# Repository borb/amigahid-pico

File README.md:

# amigahid-pico

please note: the interesting stuff goes into the [development](https://github.com/borb/amigahid-pico/tree/development) branch, so if main seems slow, check it out.

## introduction

amigahid-pico uses the rp2040 microcontroller (e.g. the raspberry pi pico) in a carrier board to attach usb input devices to a standard amiga without the need for a usb stack on the amiga itself.

it currently supports keyboards and mice and provides connection via the internal keyboard connector, the rj11/din socket on big-box amigas, and via the controller ports.

**this project is very much a work in progress.**

## **important note**

* current kicad files are for r5 pcb, pin mappings are not yet in the source tree! i have not yet generated this board as a pcb, but it is mostly identical to r4. the keyboard and controller port 1 are correct at time of writing, and will be fixed for the second controller port when the next prototype arrives.

* **always read the [errata](./doc/errata.md) section for the current pcb layout before deciding whether or not to build.**

## documentation

* [installation](./doc/installation.md)
* [hardware](./doc/hardware.md)
* [errors in revisions (errata)](./doc/errata.md)

## history

this project is a rewrite of the [amigahid](https://github.com/borb/amigahid) project to the rp2040 microcontroller.

originally, after the retirement of the arduino adk board and shortening availability of the max3421e "usb host shield" for arduino boards, the need for a cheap, easy and continually available replacement was sought.

at first, the uhs mini via a level shifter seemed ideal, but significant issues were found convincing it to work with a variety of arduino boards.

the rp2040 made sense as a target because it is widely available, has sufficient physical connections and is powerful enough to meet multiple needs.

## what is the latency of this?

i have not measured the latency, but the keyboard signals are sent out the moment they are received on the usb bus. the potential latency is likely fractionally longer than the amiga mcu but bear in mind the rp2040 is significantly faster than the standard amiga keyboard controller.

## roadmap

please see the issues tab on the [github repository](https://github.com/borb/amigahid-pico) for the current list of planned features. the tl;dr is:

normal:
* i<sup>2</sup>c display for config/status
* controller emulation
    * keyboard-based controller emulation (use udlr for directions?)
* flash memory-based configuration
* possible amiga-side control panel (using bidirectional controller port signals)
* rotary control simulation (for controlling gotek drives)

crazy talk:
* non-amiga support
* non-hidbp support
* analogue/paddle emulation
* fix some tinyusb issues (hotplug, timing-related instability)

## license

on the fence at the moment, but the current license choice is Eclipse Public License 2.0 (EPL-2.0).

## third party licenses

* µgui: this code contains 'µgui' by achim döbler; the license for this can be read at in the [display readme](./src/display/README.md)

## whuh... who?

nine <[nine@aphlor.org](mailto:nine@aphlor.org)>

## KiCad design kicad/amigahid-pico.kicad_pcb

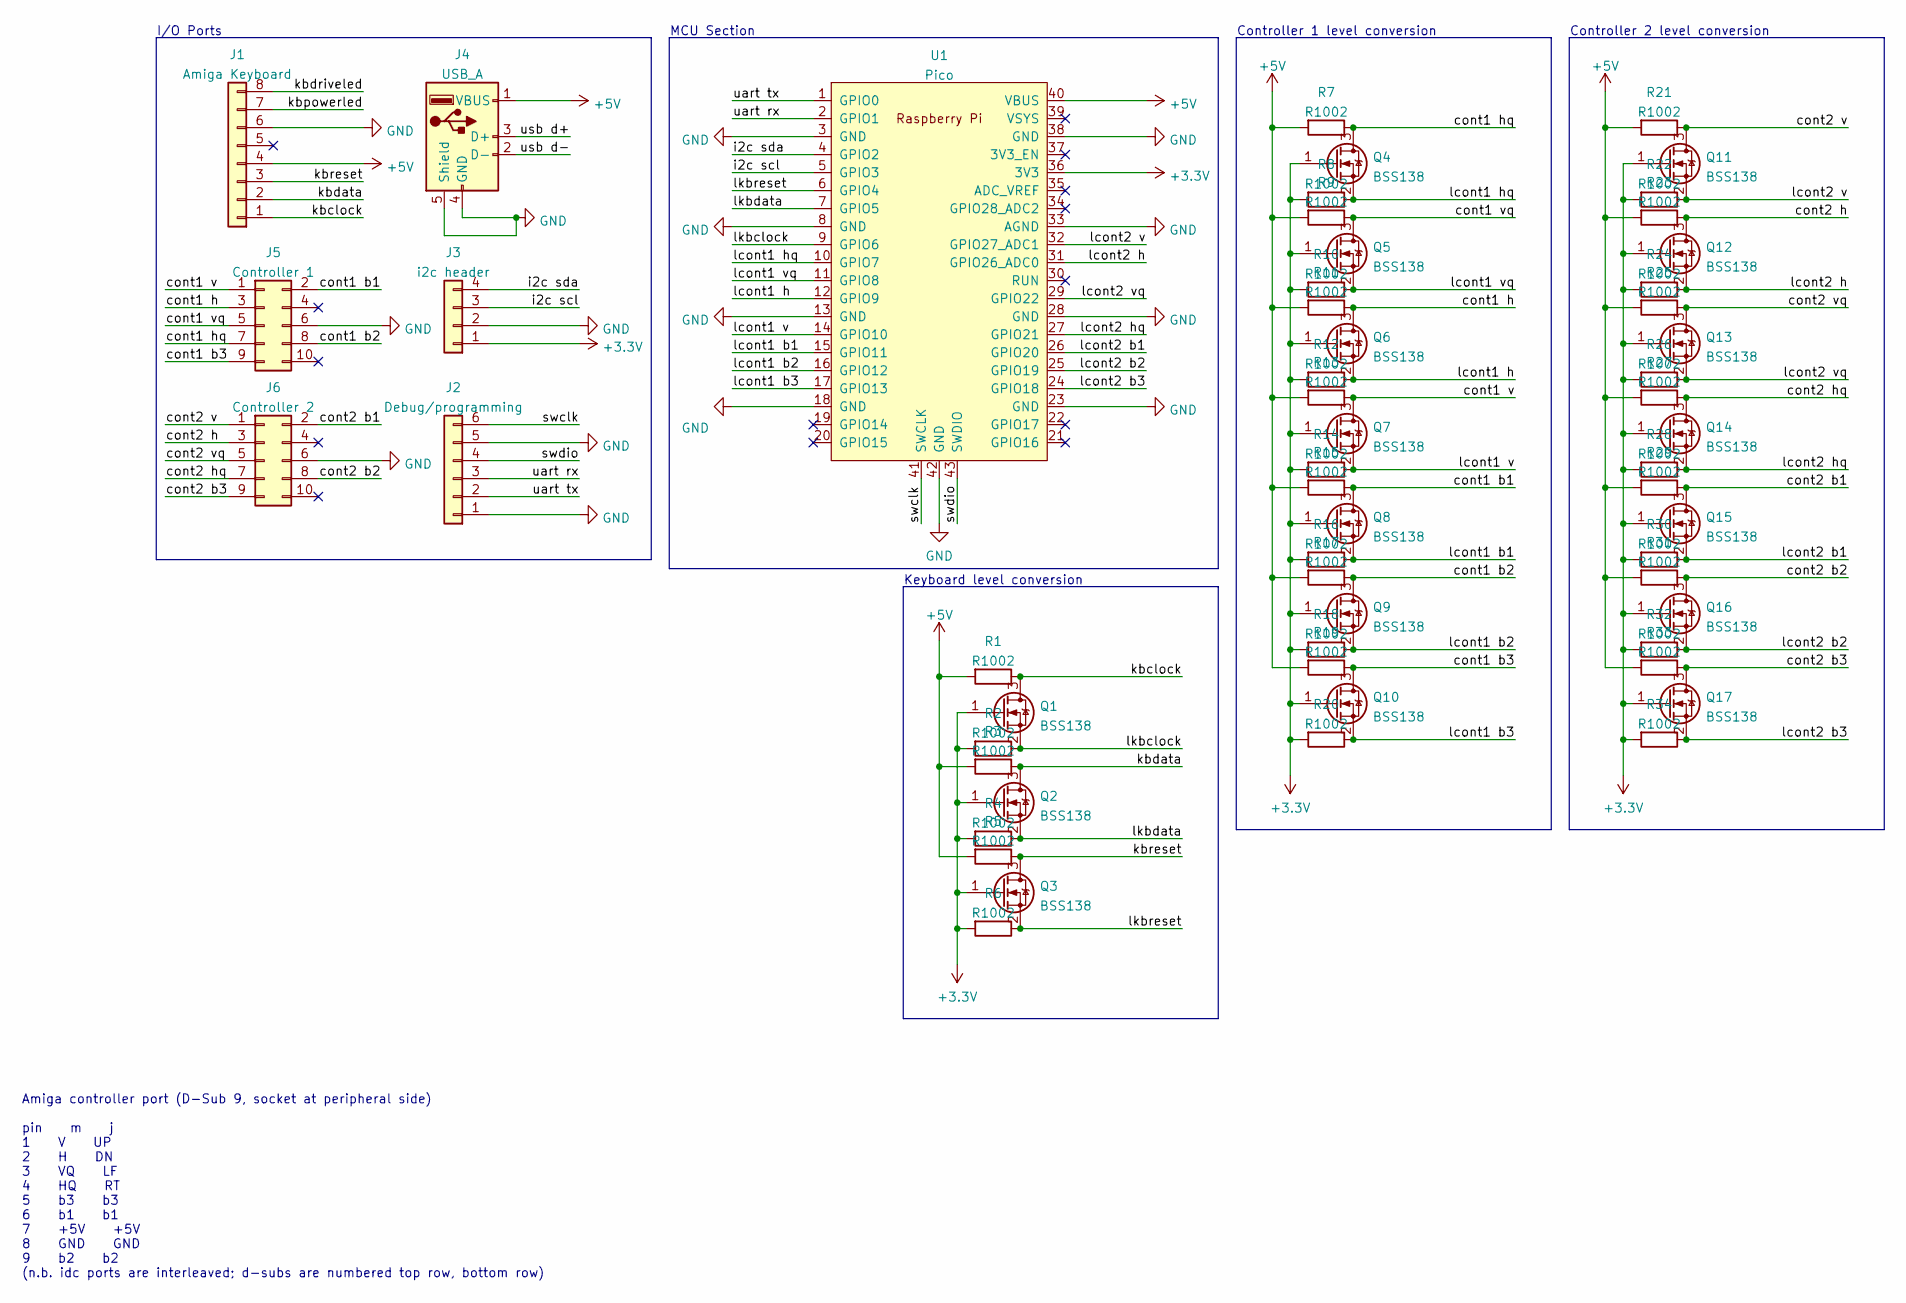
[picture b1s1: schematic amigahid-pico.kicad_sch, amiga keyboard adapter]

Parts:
J1: Amiga Keyboard; PinHeader_1x08_P2.54mm_Vertical
J2: Debug/programming; PinHeader_1x06_P2.54mm_Horizontal
J3: i2c header; PinHeader_1x04_P2.54mm_Vertical
J4: USB_A; USB_A_Molex_67643_Horizontal
J5: Controller 1; IDC-Header_2x05_P2.54mm_Vertical
J6: Controller 2; IDC-Header_2x05_P2.54mm_Vertical
Q1, Q2, Q3, Q4, Q5, Q6, Q7, Q8, Q9, Q10, Q11, Q12, Q13, Q14, Q15, Q16, Q17: BSS138; SOT-23
R1, R2, R3, R4, R5, R6, R7, R8, R9, R10, R11, R12, R13, R14, R15, R16, R17, R18, R19, R20, R21, R22, R23, R24, R25, R26, R27, R28, R29, R30, R31, R32, R33, R34: R1002; R_0603_1608Metric
U1: Pico; RPi_Pico_SMD_TH

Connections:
+3V3: J3.1, Q1.1 (G), Q2.1 (G), Q3.1 (G), Q4.1 (G), Q5.1 (G), Q6.1 (G), Q7.1 (G), Q8.1 (G), Q9.1 (G), Q10.1 (G), Q11.1 (G), Q12.1 (G), Q13.1 (G), Q14.1 (G), Q15.1 (G), Q16.1 (G), Q17.1 (G), R2.2, R4.2, R6.2, R8.2, R10.2, R12.2, R14.2, R16.2, R18.2, R20.2, R22.2, R24.2, R26.2, R28.2, R30.2, R32.2, R34.2, U1.36 (3V3)
+5V: J1.4, J4.1 (VBUS), R1.2, R3.2, R5.2, R7.2, R9.2, R11.2, R13.2, R15.2, R17.2, R19.2, R21.2, R23.2, R25.2, R27.2, R29.2, R31.2, R33.2, U1.40 (VBUS); also elsewhere on the board
/cont1 b1: J5.2, Q8.3 (D), R15.1; also elsewhere on the board
/cont1 b2: J5.8, Q9.3 (D), R17.1
/cont1 b3: J5.9, Q10.3 (D), R19.1
/cont1 h: J5.3, Q6.3 (D), R11.1
/cont1 hq: J5.7, Q4.3 (D), R7.1
/cont1 v: J5.1, Q7.3 (D), R13.1
/cont1 vq: J5.5, Q5.3 (D), R9.1
/cont2 b1: J6.2, Q15.3 (D), R29.1
/cont2 b2: J6.8, Q16.3 (D), R31.1
/cont2 b3: J6.9, Q17.3 (D), R33.1
/cont2 h: J6.3, Q12.3 (D), R23.1
/cont2 hq: J6.7, Q14.3 (D), R27.1
/cont2 v: J6.1, Q11.3 (D), R21.1
/cont2 vq: J6.5, Q13.3 (D), R25.1
/i2c scl: J3.3, U1.5 (GPIO3)
/i2c sda: J3.4, U1.4 (GPIO2)
/kbclock: J1.1, Q1.3 (D), R1.1
/kbdata: J1.2, Q2.3 (D), R3.1
/kbdriveled: J1.8
/kbpowerled: J1.7
/kbreset: J1.3, Q3.3 (D), R5.1
/lcont1 b1: Q8.2 (S), R16.1, U1.15 (GPIO11)
/lcont1 b2: Q9.2 (S), R18.1, U1.16 (GPIO12)
/lcont1 b3: Q10.2 (S), R20.1, U1.17 (GPIO13)
/lcont1 h: Q6.2 (S), R12.1, U1.12 (GPIO9)
/lcont1 hq: Q4.2 (S), R8.1, U1.10 (GPIO7)
/lcont1 v: Q7.2 (S), R14.1, U1.14 (GPIO10)
/lcont1 vq: Q5.2 (S), R10.1, U1.11 (GPIO8)
/lcont2 b1: Q15.2 (S), R30.1, U1.26 (GPIO20)
/lcont2 b2: Q16.2 (S), R32.1, U1.25 (GPIO19)
/lcont2 b3: Q17.2 (S), R34.1, U1.24 (GPIO18)
/lcont2 h: Q12.2 (S), R24.1, U1.31 (GPIO26_ADC0)
/lcont2 hq: Q14.2 (S), R28.1, U1.27 (GPIO21)
/lcont2 v: Q11.2 (S), R22.1, U1.32 (GPIO27_ADC1)
/lcont2 vq: Q13.2 (S), R26.1, U1.29 (GPIO22)
/lkbclock: Q1.2 (S), R2.1, U1.9 (GPIO6)
/lkbdata: Q2.2 (S), R4.1, U1.7 (GPIO5)
/lkbreset: Q3.2 (S), R6.1, U1.6 (GPIO4)
/swclk: J2.6, U1.41 (SWCLK)
/swdio: J2.4, U1.43 (SWDIO)
/uart rx: J2.3, U1.2 (GPIO1)
/uart tx: J2.2, U1.1 (GPIO0)
/usb d+: J4.3 (D+)
/usb d-: J4.2 (D-)
GND: J1.6, J2.1, J2.5, J3.2, J4.4 (GND), J4.5 (Shield), J5.6, J6.6, U1.3 (GND), U1.8 (GND), U1.13 (GND), U1.18 (GND), U1.23 (GND), U1.28 (GND), U1.33 (AGND), U1.38 (GND), U1.42 (GND)

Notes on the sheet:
Amiga controller port (D-Sub 9, socket at peripheral side) pin m j 1 V UP 2 H DN 3 VQ LF 4 HQ RT 5 b3 b3 6 b1 b1 7 +5V +5V 8 GND GND 9 b2 b2 (n.b. idc ports are interleaved; d-subs are numbered top row, bottom row)
MCU Section
I/O Ports
Controller 1 level conversion
Controller 2 level conversion
Keyboard level conversion

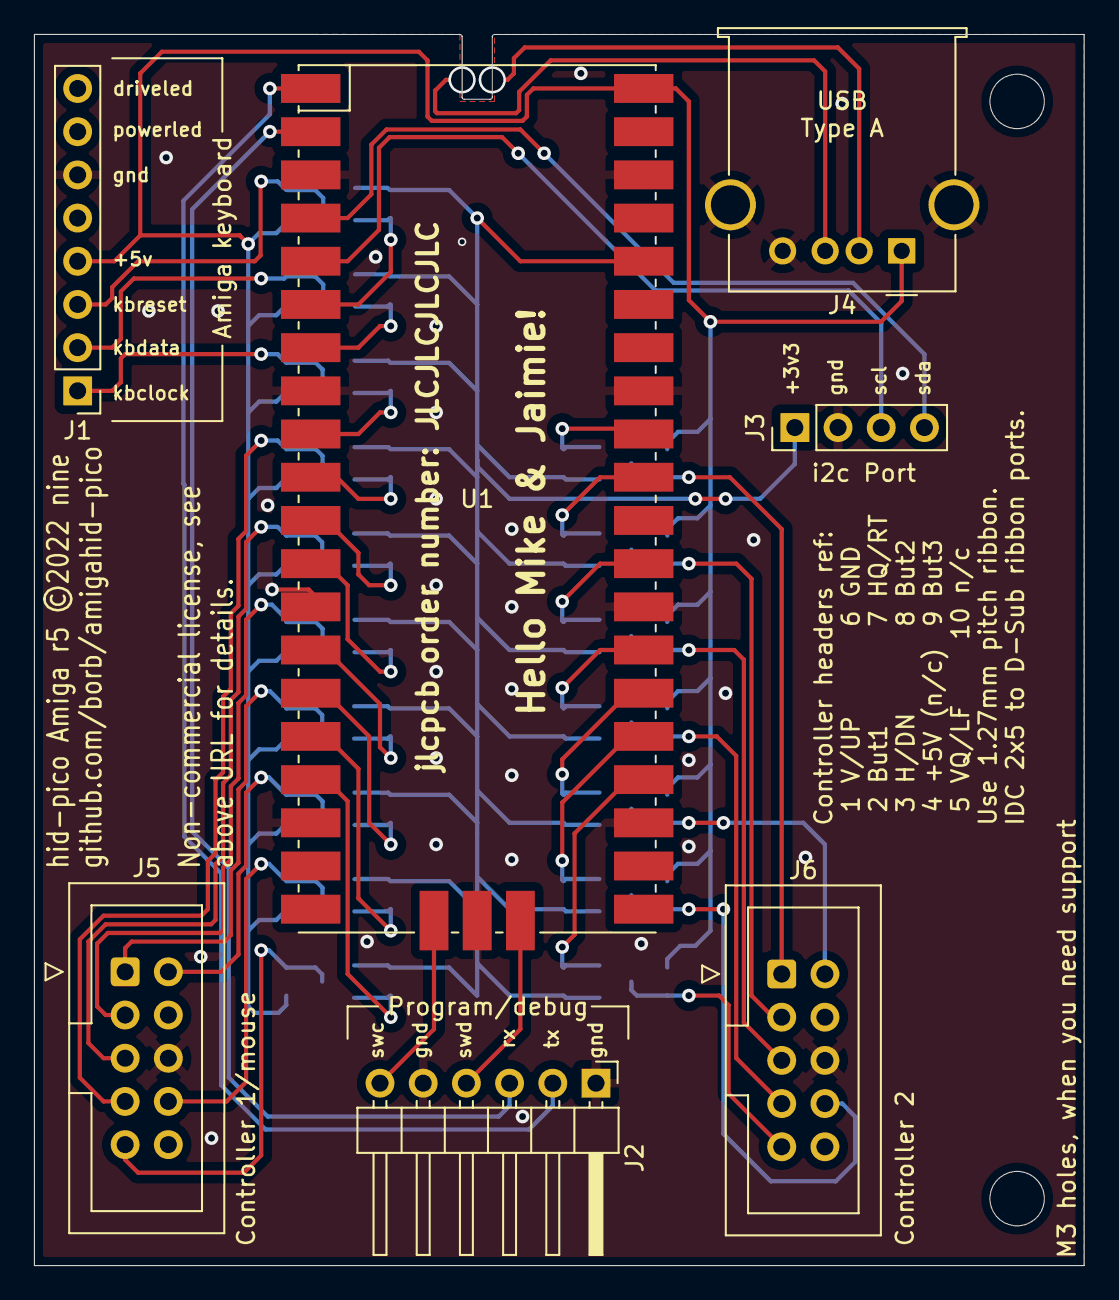
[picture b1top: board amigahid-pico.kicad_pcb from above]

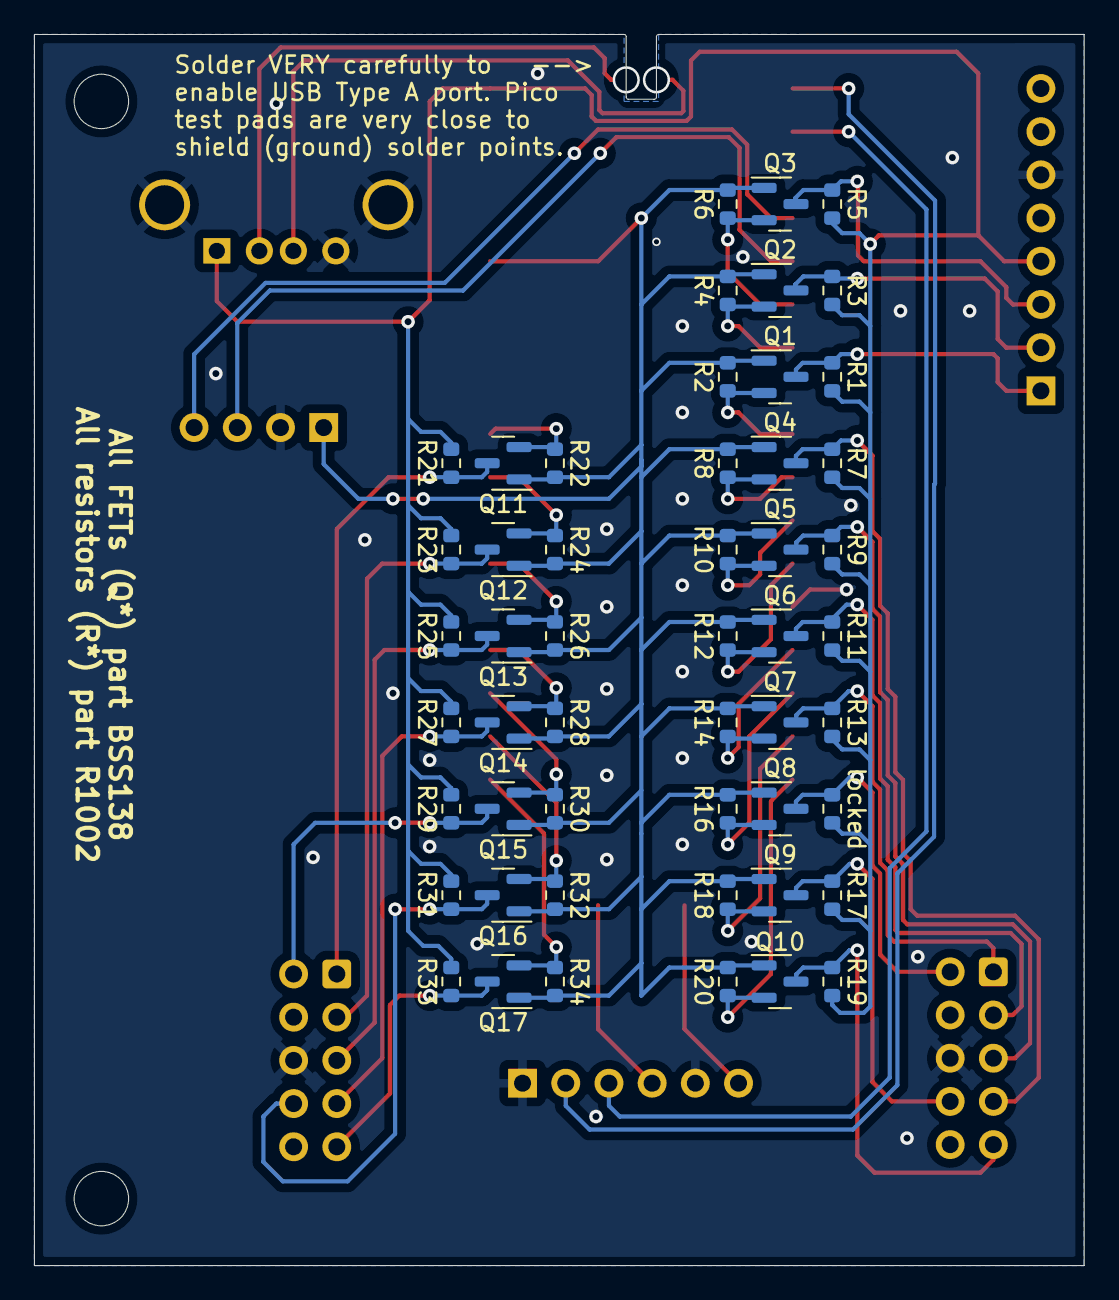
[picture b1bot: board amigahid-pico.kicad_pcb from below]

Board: 2 copper layers, 61.7 x 72.4 mm, 60 parts (51 on the bottom side), 43 nets.

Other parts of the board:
REF01, REF02: MountingHole_3.2mm_M3
locked: R1002; R_0603_1608Metric

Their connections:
+5V: locked.2; also elsewhere on the board
/cont1 b1: locked.1; also elsewhere on the board

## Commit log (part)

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2021-11-18 initial structure for cmake project
2021-11-18 use sdk kept internally to the path (so it can be submoduled)
2021-11-18 put src/ in the include path, build all project files
2021-12-20 oh look, a readme
2021-12-20 before i've even done an initial push, an update
2021-12-30 whoops; forgetting to call this meant no worky
2021-12-30 reorder pins to match the amiga keyboard header better
2021-12-30 handle modifiers (no caps lock, yet)
2021-12-30 readme update
2021-12-30 no reset, so far
2021-12-30 fix ref
2021-12-31 compile-time options
2021-12-31 add caps lock and reset code
2021-12-31 add build notes
2022-01-01 pcb proto - DO NOT BUILD (untested)
2022-01-01 remove useless file
2022-01-01 add small note about the board design ground plane
2022-01-01 ha, missing static meant caps lock no worky
2022-01-01 warn that $ff isn't being sent
2022-01-01 handle ctrl
2022-01-01 slightly more meaningful debug output
2022-01-01 fix the trinity check so two ctrl doesn't confuse it
2022-01-08 move caps lock tracking around a bit
2022-01-08 fix fault causing keyup not to be sent to amiga
2022-01-08 pass dev_addr & instance around so we can call set_report()
2022-01-26 expand upon hotplug issues
2022-01-28 move output ahprintf, add flag, keyb pio stub
2022-01-28 mouse stub
2022-01-29 yeah, that's actually been done
2022-01-29 this is in usb_hid.c but it's not working
2022-02-03 documentation, start of mouse stuff
2022-02-04 make the table readable without markdown
2022-02-04 wip amiga mouse emulation (untested)
    this must be the fourth rewrite; committing as i think this might behave better. there may be issues with the pulse interval, which is currently 375us. 37.5ms is probably a better timing, but i want 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
2022-02-10 moniker to denote where debug message comes from
2022-02-11 fix mouse motion. it works!
2022-02-15 whilst i'm routing the pcb, commit this; maybe sub to change
2022-02-27 update schematic to use fets, txs0108 not suitable (+)
    the txs0108 doesn't do well with capacitive loads, so the reset line
    keeps dropping too low (around 3.8v or below); the knock-on effect is
    that the amiga keeps resetting itself but moreover controller ports do
    not work correctly (if at all), and the keyboard behaves erratically
    (though the keycodes get through, the voltage levels are too low to
    match spec).
2022-03-03 add rev2 pcb design (ALL THE VIAS)
2022-03-03 update board picture
2022-03-12 add dpi motion division support
2022-03-15 don't raise output; set dir=in and let amiga do it
    cryptic short message, but by not raising the output to high level we're
    not actively sending a high signal, instead relying on the amiga doing
    so. ultimately, with the current mosfet-based design, it doesn't matter
    a great deal: either side of the voltage conversion uses a pullup, so a
    current is raised regardless, but the pico's drain to 0V (active low)
    will be unaffected.
2022-03-26 raise enum bufsize, device count. hubs work!
2022-03-28 add ssd1306 library from https://github.com/daschr/pico-ssd1306
2022-03-28 remove a lot of unneeded stuff from the readme
2022-03-28 more backstory waffle :D
2022-04-10 Use open drain outputs for keyboard interface
2022-04-10 pcb rev 4
2022-04-10 r4 pcb update
2022-04-10 bad filename; my error
2022-04-10 change to inline, set 0 before direction for safety
2022-04-10 restore comments, parity between mouse open drain change
2022-04-12 Update capslock LED
2022-04-17 making slightly more coherent
2022-04-18 remove irritating message which shouldn't have been committed :D
2022-04-21 some tidy up of the ssd1306 code (large fonts not working)
2022-04-21 add pin mappings for rev 4 board, make default
2022-04-21 add compile opt for board revision
2022-04-21 readd m3 holes to board; update readme graphic
2022-07-06 some not-quite-working display testing sitting in the tree for a while
2022-07-09 wip debug console tidyup
2022-07-09 spelling mistake; aqm, not amq
2022-07-09 comment this out for a bit (it needs replacing with dma methods)
2022-07-09 if using an enum, use the damned enum type
2022-07-09 remove a lot of debug noise
2022-07-09 big old refactor of the translation to move amiga stuff into amiga code
2022-09-04 switch from pico-sdk's tusb to upstream 0.14.0; fixes mouse motion bugs
2022-09-04 drop note regarding hubs and forks
2022-09-04 splitting up readme, removing verbose chunks
2022-09-25 add indicator led position; use pico default (since we use that)
2022-10-02 update with cmake stub from latest pico-sdk
2022-10-13 wip dma-driven i2c display; note: blocks for 100ms between ops!
    uses ugui for display writing. need to write isr-driven queue for i2c
    transactions.
    gh issue #5
2022-10-15 wip isr driven linked list (not quite working)
2022-10-17 fix linked list, turn off malloc mutex, tidy
2022-10-17 sample text whilst i work on positioning
2022-10-17 use 5x12 pixel font positioned in a 5x16 area, y+2 offset
2022-10-17 crlf -> lf
2022-10-19 enable all warnings, warnings are errors
2022-10-19 unused variable
2022-10-19 comment unused code (think it can be removed)
2022-10-19 dbg counters case for unknown devices
2022-10-19 change compile options to definitions for portability
2022-10-19 fix mismatching indentation on enum
2022-10-19 c style reformatting hints
2022-10-19 stub of check for device presence
2022-10-31 repoint display write to a noop when not available
2022-10-31 ssd1306 dma display support, clang-format config (#20)
    * add indicator led position; use pico default (since we use that)
    * remove older ssd1306 things; prepping for dma code
    * update with cmake stub from latest pico-sdk
    * wip dma-driven i2c display; note: blocks for 100ms between ops!
    uses ugui for display writing. need to write isr-driven queue for i2c
    transactions.
2022-10-31 Put usable data on the display (#21)
    * output usb plug & kb data to i2c display
2022-10-31 update to current tusb config
2022-10-31 Update to current tinyusb config standard (#22)
    * update to current tusb config
2023-03-20 Fix compilation on Ubuntu 22.04.2 LTS
    Compiler: (Ubuntu 22.04.2 LTS)
    gcc version 10.3.1 20210621 (release) (15:10.3-2021.07-4)
    Error:
    [100%] Linking CXX executable amigahid-pico.elf
    .../ld: CMakeFiles/amigahid-pico.dir/util/debug_cons.c.obj:(.bss.disp_write+0x0):
    multiple definition of `disp_write';
2023-03-21 Fix compilation on Ubuntu 22.04.2 LTS (#25)
    Compiler: (Ubuntu 22.04.2 LTS)
    gcc version 10.3.1 20210621 (release) (15:10.3-2021.07-4)
    Error:
    [100%] Linking CXX executable amigahid-pico.elf
    .../ld: CMakeFiles/amigahid-pico.dir/util/debug_cons.c.obj:(.bss.disp_write+0x0):
    multiple definition of `disp_write';
2023-03-21 header for int types
2023-04-10 add note about development
2023-06-28 bring in lufa's hid report descriptor parser code
2023-07-17 remove previous wip parser effort
2023-07-22 bump hub and hid counts
2023-07-22 quick & dirty 'program via swd' script
2023-07-24 fix compile failure due to potential of missing return
2023-07-24 only switch mouse to report mode if we have a report descriptor
    potentially, if a mouse is a very simple device, it could only have a hidbp mode and no report mode, so don't try it if we have no descriptor
2023-07-28 most of the code to handle hid report separate to hidbp
    need to add code to translate buttons, wheel and motion to amiga actions
2023-08-15 add a container for repeatable builds
2023-08-15 ignore kicad backups
2024-03-20 hold clk low for 500ms to reset a2k/3k/4k
2024-08-12 don't make serial messages conditional
2024-08-12 use boolean for pointlessness in infinite loops
2024-08-12 use 16-bit integers for mouse motion as per hid report mode
2024-08-12 i2c display won't mix in serial debug messages any longer; rename of dbgcons to come later
2024-08-12 add git commit hash and dirty status as a C definition for code use
2024-08-12 add serial console logging back in a simplistic fashion
2025-08-03 this isn't working. and it's causing me hair loss.
2025-08-04 switch tinyusb to 0.18.0
2025-08-04 unfinished hack - this will make report mode mouse work, might break keyboard (works on test dell)
2025-08-04 pointer of where to put the report mode switch
2025-08-04 this todo is now resolved; report_info_t and ReportInfo_t are distinct
2026-01-18 prebuilt versions whilst i'm occupied with a busy life
2026-03-28 update pico-sdk to 2.2.0, drop tinyusb as we're using pico-sdk version, compatible with cmake 4 now
2026-03-28 Fix build for current version cmake & pico-sdk (#39)
2026-03-28 barebones ci file
2026-03-28 checkout v4 uses old node, use v6
2026-03-28 add make and gcc for arm cortex-m
2026-03-28 submodules can be checked out by actions/checkout
2026-03-28 i can't spell
2026-03-29 set target board
2026-03-29 this is now unused
2026-03-29 allow pico platform & board to be overriden in cmake -D
2026-03-29 add build matrix to cover multiple board types
2026-03-29 let's get the right action name this time
2026-03-29 use a more elaborate mechanism to merge builds
2026-03-29 fix syntax error
2026-03-29 unique naming for artifacts
2026-03-29 update build instructions
2026-03-29 prebuilt is no longer required; actions now handles this
2026-03-29 Add CI build & remove old devel prebuild (#40)
2026-03-29 Add CI build & remove old devel prebuild (#40) (#41)
2026-04-04 fix docs on setting board type
2026-04-04 fix held ctrl-amiga-amiga (#37)
    move CLK set high to amiga_release_reset
    disable key sending whilst in reset - which would change CLK state
2026-04-04 Release 0.1.1 (#42)
    * Add CI build & remove old devel prebuild (#40)
    * fix held ctrl-amiga-amiga
    move CLK set high to amiga_release_reset
    disable key sending whilst in reset - which would change CLK state
    * explain why keycodes sent not in reset, tidy formatting
    * fix docs on setting board type
2026-04-18 platform/amiga: fix quadrature mouse delta handling
    Keep mouse motion in 16-bit accumulators and preserve divider
    remainders between output batches.
    This stops small axis-only movement from being dropped before it
    reaches the Amiga quadrature generator. It also aligns the initial
    quadrature state with the idle line levels used at init.
2026-04-18 debug: gate input tracing behind build flags
    Add DEBUG_MOUSE and DEBUG_KEYBOARD build options so the
    per-report mouse trace and per-key keyboard trace can be
    compiled out of the default build.
    This keeps the debug code available when needed without
    forcing the hot input paths to update UART and the OLED on
    every event.
2026-04-18 platform/amiga: queue mouse motion across cores
    Replace the shared x/y accumulators with a queue-backed handoff
    between the USB host side and the quadrature output loop.
    This removes the racy cross-core read-modify-write pattern that
    could drop motion under load. It also lets the quadrature loop
    merge newly arrived deltas between output steps.
2026-04-19 debug: gate HID status behind a build flag
    Add DEBUG_HID_STATUS so the OLED HID mount and receive status
    line can be compiled out of the default build.
    This keeps the status display available for diagnosis without
    forcing line 2 updates in normal use.
2026-04-19 input: track USB HID state by source
    Move keyboard and mouse state out of usb_hid.c into a shared input
    bridge and allocate slots by device address plus interface number.
    Reset that state on mount and disconnect so each source keeps its
    own keys, buttons and LED state.
    This avoids cross-talk between composite or multi-device HID
    setups and gives USB and Bluetooth a common path into the Amiga

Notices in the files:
kicad/amigahid-pico.kicad_pcb:
hid-pico Amiga r5 ©️2022 nine
